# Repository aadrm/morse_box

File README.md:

# morse_box

Very simple prop made for [Breakout Escape Room](https://breakout-escaperoom.de), consists of an Arduino nano that uses a buzzer to emit morse code signals repetively as long as it's powered.

## Contents:
* FreeCAD: mount for the pcb 
* Kikad: Diagrams and pcb layout
* Arduino program

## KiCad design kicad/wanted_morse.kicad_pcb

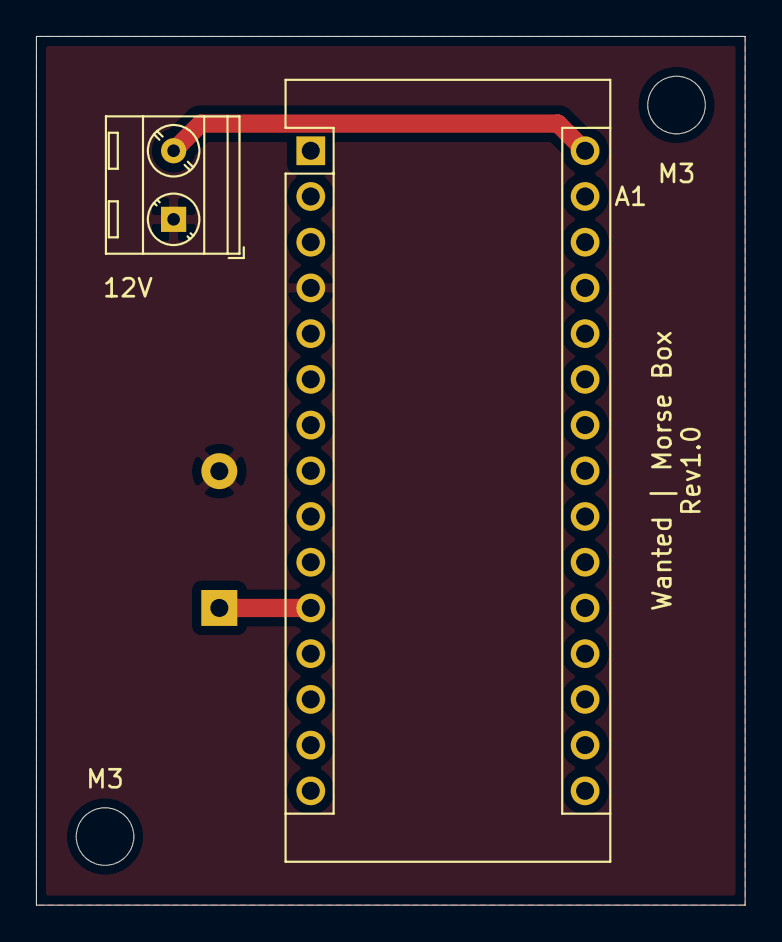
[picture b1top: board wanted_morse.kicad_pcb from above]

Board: 2 copper layers, 39.4 x 48.3 mm, 5 parts (1 on the bottom side), 3 nets.

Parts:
12V: RT03402HBLC3.81mm; TerminalBlock_MetzConnect_Type086_RT03402HBLC_1x02_P3.81mm_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
A1: Arduino_Nano_v3.x; Arduino_Nano
BZ1: Buzzer; Buzzer_12x9.5RM7.6
M3, M3#2: MountingHole_2.2mm_M2

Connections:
+12V: 12V.2, A1.30
GND: 12V.1, A1.4, BZ1.2
unnamed: A1.11, BZ1.1

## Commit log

2021-09-22 arduino file
2021-09-22 added kicad files
2021-09-22 removed gbr files'
2021-09-22 added 3d printable mount
2021-09-22 added gbrjob to gitignore
2021-09-22 deleted old gbrjob
2021-09-22 added drill files to gitignore
2021-09-23 buzzer placed to the back side
2021-09-23 added description and contents
2021-09-23 fixed list of contents
2021-09-23 mount readme added
2022-03-01 fixed first comment typo
2022-04-25 Update wanted_morse.ino
    added comments
2023-03-19 ignore kicad backups
2023-03-20 updated kicad files
2023-03-20 Add .vscode
2023-03-20 builtin led blinks with tone
